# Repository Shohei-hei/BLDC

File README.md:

# BLDC
BLDC hardware and software

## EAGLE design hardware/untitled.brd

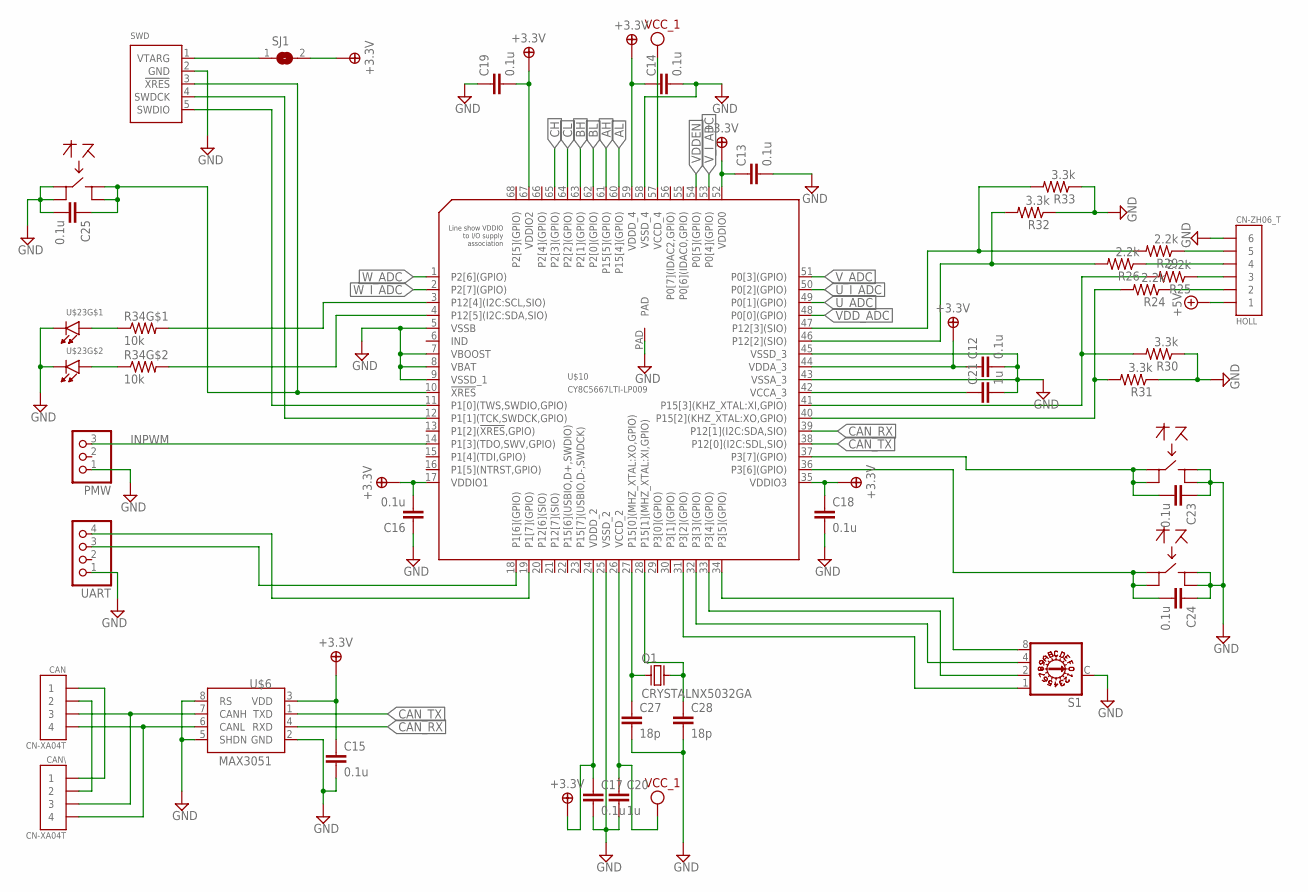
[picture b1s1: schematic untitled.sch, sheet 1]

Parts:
C12, C13, C14, C15, C16, C17, C18, C19, C23, C24, C25: 0.1u; C1005
C20, C21: 1u; C1608
C27, C28: 18p; C1608
CAN: CN-XA04T; XA04
CAN\: CN-XA04T; XA04
HOLL: CN-ZH06_T; ZH06
PMW: PINHD-1X03_2.54-S; 1X03-S
Q1: CRYSTALNX5032GA; NX5032GA
R24, R25, R26, R29: 2.2k; R1005
R30, R31, R32, R33: 3.3k; R1005
R34: 10k; R1005*2
RESET: SWITCH_4PALPS; SKRP
S1: P103_AKI; SW_ROT_5
SJ1: SJ
SWD: WRITE-FOR-PSOC3/4/5LP_ZH; ZH05
U$6: MAX3051; SOIC8
U$10: CY8C5667LTI-LP009; QFN68_8X8
U$23: LED2_SML522; LED1315
UART: PINHD-1X04_2.54-S; 1X04-S
USER1, USER2: SWITCH_4PALPS; SKRP

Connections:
3.3V: C12.1, C13.1, C14.1, C15.1, C16.2, C17.1, C18.1, C19.2, SJ1.2, U$6.3 (VDD), U$10.17 (VDDIO1), U$10.24 (VDDD_2), U$10.35 (VDDIO3), U$10.44 (VDDA_3), U$10.52 (VDDIO0), U$10.59 (VDDD_4), U$10.67 (VDDIO2); also elsewhere on the board
+5V: HOLL.1; also elsewhere on the board
AH: U$10.61 (P15[5](GPIO)); also elsewhere on the board
AL: U$10.60 (P15[4](GPIO)); also elsewhere on the board
BH: U$10.63 (P2[1](GPIO)); also elsewhere on the board
BL: U$10.62 (P2[0](GPIO)); also elsewhere on the board
CAN_RX: U$6.4 (RXD), U$10.39 (P12[1](I2C:SDA,SIO))
CAN_TX: U$6.1 (TXD), U$10.38 (P12[0](I2C:SDL,SIO))
CH: U$10.65 (P2[3](GPIO)); also elsewhere on the board
CL: U$10.64 (P2[2](GPIO)); also elsewhere on the board
GND: C12.2, C13.2, C14.2, C15.2, C16.1, C17.2, C18.2, C19.1, C20.2, C21.2, C23.1, C24.1, C25.2, C27.2, C28.2, HOLL.6, PMW.1, R30.1, R31.1, R32.1, R33.1, RESET.1, RESET.2, S1.C, SWD.2 (GND), U$6.2 (GND), U$6.5 (SHDN), U$6.8 (RS), U$10.5 (VSSB), U$10.7 (VBOOST), U$10.8 (VBAT), U$10.9 (VSSD_1), U$10.25 (VSSD_2), U$10.43 (VSSA_3), U$10.45 (VSSD_3), U$10.58 (VSSD_4), U$10.PAD, U$23.2 (C), U$23.4 (C), UART.1, USER1.3, USER1.4, USER2.3, USER2.4; also elsewhere on the board
INPWM: PMW.3, U$10.14 (P1[3](TDO,SWV,GPIO))
unnamed: U$10.18 (P1[6](GPIO)), UART.3
unnamed: S1.8, U$10.34 (P3[5](GPIO))
unnamed: R29.2, R33.2, U$10.47 (P12[3](SIO))
unnamed: C21.1, U$10.42 (VCCA_3)
unnamed: CAN.PIN1 (1), CAN\.PIN1 (1)
unnamed: CAN.PIN2 (2), CAN\.PIN2 (2)
unnamed: CAN.PIN3 (3), CAN\.PIN3 (3), U$6.7 (CANH)
unnamed: CAN.PIN4 (4), CAN\.PIN4 (4), U$6.6 (CANL)
unnamed: C23.2, U$10.37 (P3[7](GPIO)), USER1.1, USER1.2
unnamed: C24.2, U$10.36 (P3[6](GPIO)), USER2.1, USER2.2
unnamed: SWD.5 (SWDIO), U$10.11 (P1[0](TWS,SWDIO,GPIO))
unnamed: SWD.4 (SWDCK), U$10.12 (P1[1](TCK,SWDCK,GPIO))
unnamed: C27.1, Q1.1, U$10.27 (P15[0](MHZ_XTAL:XO,GPIO))
unnamed: C28.1, Q1.2, U$10.28 (P15[1](MHZ_XTAL:XI,GPIO))
unnamed: C25.1, RESET.3, RESET.4, SWD.3 (!XRES), U$10.10 (!XRES)
unnamed: U$10.19 (P1[7](GPIO)), UART.4
unnamed: S1.4, U$10.32 (P3[3](GPIO))
unnamed: S1.1, U$10.31 (P3[2](GPIO))
unnamed: R26.2, R32.2, U$10.46 (P12[2](SIO))
unnamed: S1.2, U$10.33 (P3[4](GPIO))
unnamed: R24.2, R31.2, U$10.40 (P15[2](KHZ_XTAL:XO,GPIO))
unnamed: R25.2, R30.2, U$10.41 (P15[3](KHZ_XTAL:XI,GPIO))
unnamed: HOLL.2, R24.1
unnamed: HOLL.3, R25.1
unnamed: HOLL.4, R26.1
unnamed: HOLL.5, R29.1
unnamed: SJ1.1, SWD.1 (VTARG)
unnamed: R34.A1 (1), U$23.1 (A)
unnamed: R34.B1 (1), U$23.3 (A)
unnamed: R34.B2 (2), U$10.4 (P12[5](I2C:SDA,SIO))
unnamed: R34.A2 (2), U$10.3 (P12[4](I2C:SCL,SIO))
U_ADC: U$10.49 (P0[1](GPIO)); also elsewhere on the board
U_I_ADC: U$10.50 (P0[2](GPIO)); also elsewhere on the board
VCC_1: C20.1, U$10.26 (VCCD_2), U$10.57 (VCCD_4)
VDDEN: U$10.54 (P0[5](GPIO)); also elsewhere on the board
VDD_ADC: U$10.48 (P0[0](GPIO)); also elsewhere on the board
V_ADC: U$10.51 (P0[3](GPIO)); also elsewhere on the board
V_I_ADC: U$10.53 (P0[4](GPIO)); also elsewhere on the board
W_ADC: U$10.1 (P2[6](GPIO)); also elsewhere on the board
W_I_ADC: U$10.2 (P2[7](GPIO)); also elsewhere on the board

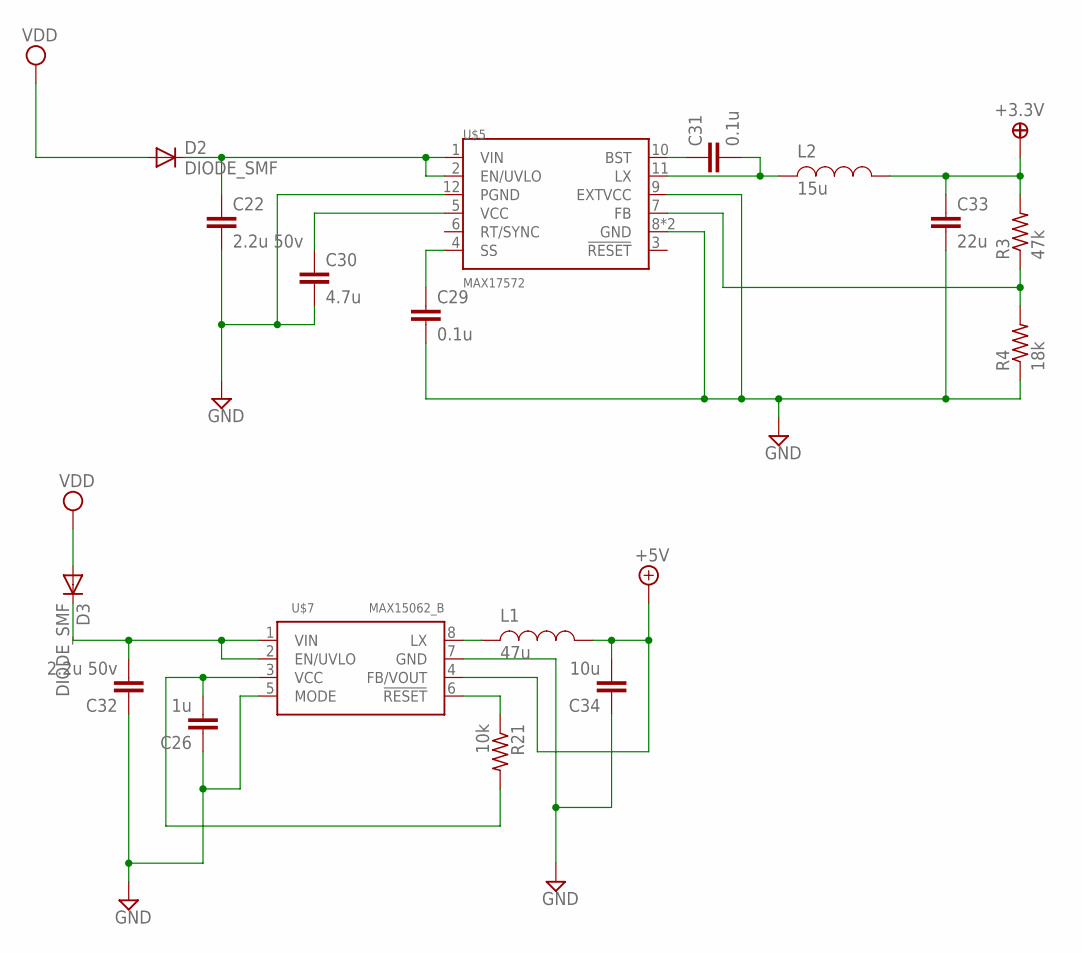
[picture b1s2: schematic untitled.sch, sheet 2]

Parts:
C22, C32: 2.2u 50v; C3216
C26: 1u; C1608
C29, C31: 0.1u; C1005
C30: 4.7u; C2012
C33: 22u; C3216
C34: 10u; C1608
D2, D3: DIODE_SMF; DO-219AB(SMF)
L1: 47u; L2518
L2: 15u; SRN4018
R3: 47k; R1005
R4: 18k; R1005
R21: 10k; R1005
U$5: MAX17572; TDFN12-3X3
U$7: MAX15062_B; TDFN08_2X2(NO_BOTTOM)

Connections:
3.3V: C33.1, L2.P$2, R3.2; also elsewhere on the board
+5V: C34.2, L1.P$2, U$7.4 (FB/VOUT); also elsewhere on the board
GND: C22.2, C26.1, C29.2, C30.2, C32.1, C33.2, C34.1, R4.1, U$5.8 (GND), U$5.9 (EXTVCC), U$5.12 (PGND), U$5.EPAD (GND), U$7.5 (MODE), U$7.7 (GND); also elsewhere on the board
unnamed: C32.2, D3.C, U$7.1 (VIN), U$7.2 (EN/UVLO)
unnamed: C22.1, D2.C, U$5.1 (VIN), U$5.2 (EN/UVLO)
unnamed: C29.1, U$5.4 (SS)
unnamed: C30.1, U$5.5 (VCC)
unnamed: R3.1, R4.2, U$5.7 (FB)
unnamed: C31.2, L2.P$1, U$5.11 (LX)
unnamed: C31.1, U$5.10 (BST)
unnamed: C26.2, R21.2, U$7.3 (VCC)
unnamed: R21.1, U$7.6 (!RESET)
unnamed: L1.P$1, U$7.8 (LX)
VDD: D2.A, D3.A; also elsewhere on the board

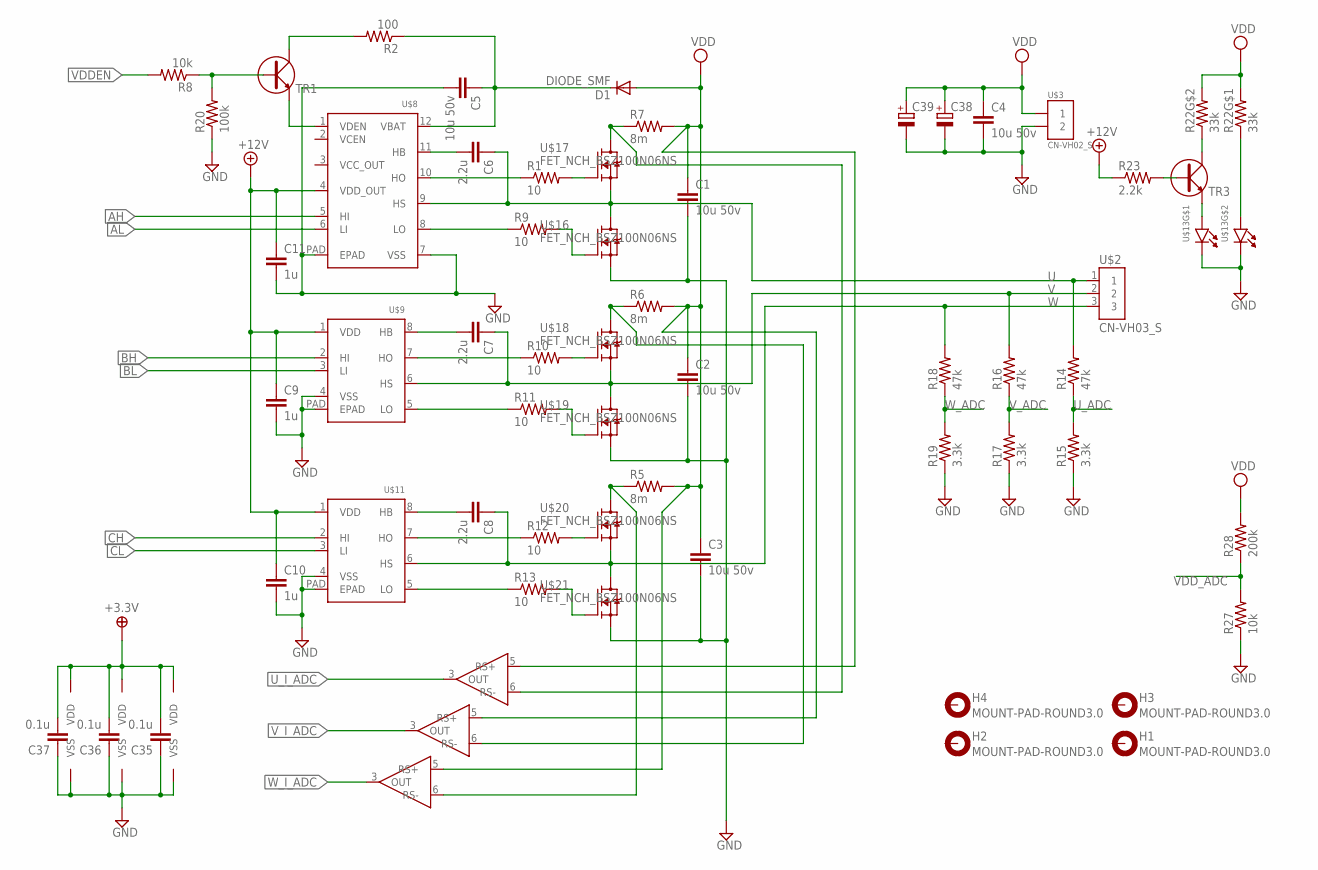
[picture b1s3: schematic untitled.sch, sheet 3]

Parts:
C1, C2, C3, C4, C5: 10u 50v; C3216
C6, C7, C8: 2.2u; C1005
C9, C10, C11: 1u; C1608
C35, C36, C37: 0.1u; C1005
C38: CPOL-EUG; PANASONIC_G
C39: CPOL-EUE5-13; E5-13
D1: DIODE_SMF; DO-219AB(SMF)
H1, H2, H3, H4: MOUNT-PAD-ROUND3.0; 3,0-PAD
R1, R9, R10, R11, R12, R13: 10; R1608
R2: 100; R1005
R5, R6, R7: 8m; R3216
R8, R27: 10k; R1005
R14, R16, R18: 47k; R1005
R15, R17, R19: 3.3k; R1005
R20: 100k; R1005
R22: 33k; R1005*2
R23: 2.2k; R1005
R28: 200k; R1005
TR1, TR3: TR_NTR; SOT-23-3
U$2: CN-VH03_S; VH03-S
U$3: CN-VH02_S; VH02-S
U$8: HIP2104; DFN_4X4_12LD
U$9, U$11: HIP2103; DFN_3X3_8L
U$13: LED2_SML522; LED1315
U$14, U$15, U$22: MAX40010; SOT-23-6
U$16, U$17, U$18, U$19, U$20, U$21: FET_NCH_BSZ100N06NS; TSDSON-8

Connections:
3.3V: C35.2, C36.2, C37.2, U$14.4 (VDD), U$15.4 (VDD), U$22.4 (VDD); also elsewhere on the board
+12V: C9.1, C10.1, C11.1, R23.1, U$8.4 (VDD_OUT), U$9.1 (VDD), U$11.1 (VDD)
AH: U$8.5 (HI); also elsewhere on the board
AL: U$8.6 (LI); also elsewhere on the board
BH: U$9.2 (HI); also elsewhere on the board
BL: U$9.3 (LI); also elsewhere on the board
CH: U$11.2 (HI); also elsewhere on the board
CL: U$11.3 (LI); also elsewhere on the board
GND: C1.2, C2.2, C3.2, C4.2, C5.2, C9.2, C10.2, C11.2, C35.1, C36.1, C37.1, C38.-, C39.-, R15.1, R17.1, R19.1, R20.1, R27.1, U$3.1 (2), U$8.7 (VSS), U$8.PAD (EPAD), U$9.4 (VSS), U$9.PAD (EPAD), U$11.4 (VSS), U$11.PAD (EPAD), U$13.2 (C), U$13.4 (C), U$14.2 (VSS), U$15.2 (VSS), U$16.1 (S), U$16.2 (S), U$16.3 (S), U$16.123 (S), U$19.1 (S), U$19.2 (S), U$19.3 (S), U$19.123 (S), U$21.1 (S), U$21.2 (S), U$21.3 (S), U$21.123 (S), U$22.2 (VSS); also elsewhere on the board
unnamed: R13.2, U$21.4 (G)
unnamed: R13.1, U$11.5 (LO)
unnamed: R11.2, U$19.4 (G)
unnamed: R12.1, U$11.7 (HO)
unnamed: R9.2, U$16.4 (G)
unnamed: R12.2, U$20.4 (G)
unnamed: R6.1, U$15.6 (RS-), U$18.5 (D), U$18.6 (D), U$18.7 (D), U$18.8 (D), U$18.5678 (D)
unnamed: C8.2, U$11.8 (HB)
unnamed: C7.2, U$9.8 (HB)
unnamed: C6.2, U$8.11 (HB)
unnamed: R5.1, U$20.5 (D), U$20.6 (D), U$20.7 (D), U$20.8 (D), U$20.5678 (D), U$22.6 (RS-)
unnamed: TR1.2 (E), U$8.1 (VDEN)
unnamed: R8.1, R20.2, TR1.1 (B)
unnamed: R11.1, U$9.5 (LO)
unnamed: R10.2, U$18.4 (G)
unnamed: R10.1, U$9.7 (HO)
unnamed: R9.1, U$8.8 (LO)
unnamed: R2.2, TR1.3 (C)
unnamed: R7.1, U$14.6 (RS-), U$17.5 (D), U$17.6 (D), U$17.7 (D), U$17.8 (D), U$17.5678 (D)
unnamed: C5.1, D1.C, R2.1, U$8.12 (VBAT)
unnamed: R23.2, TR3.1 (B)
unnamed: R1.2, U$17.4 (G)
unnamed: R1.1, U$8.10 (HO)
unnamed: R22.B1 (1), TR3.3 (C)
unnamed: TR3.2 (E), U$13.1 (A)
unnamed: R22.A1 (1), U$13.3 (A)
U: C6.1, R14.2, U$2.1, U$8.9 (HS), U$16.5 (D), U$16.6 (D), U$16.7 (D), U$16.8 (D), U$16.5678 (D), U$17.1 (S), U$17.2 (S), U$17.3 (S), U$17.123 (S)
U_ADC: R14.1, R15.2; also elsewhere on the board
U_I_ADC: U$14.3 (OUT); also elsewhere on the board
V: C7.1, R16.2, U$2.2, U$9.6 (HS), U$18.1 (S), U$18.2 (S), U$18.3 (S), U$18.123 (S), U$19.5 (D), U$19.6 (D), U$19.7 (D), U$19.8 (D), U$19.5678 (D)
VDD: C1.1, C2.1, C3.1, C4.1, C38.+, C39.+, D1.A, R5.2, R6.2, R7.2, R22.A2 (2), R22.B2 (2), R28.2, U$3.2 (1), U$14.5 (RS+), U$15.5 (RS+), U$22.5 (RS+); also elsewhere on the board
VDDEN: R8.2; also elsewhere on the board
VDD_ADC: R27.2, R28.1; also elsewhere on the board
V_ADC: R16.1, R17.2; also elsewhere on the board
V_I_ADC: U$15.3 (OUT); also elsewhere on the board
W: C8.1, R18.2, U$2.3, U$11.6 (HS), U$20.1 (S), U$20.2 (S), U$20.3 (S), U$20.123 (S), U$21.5 (D), U$21.6 (D), U$21.7 (D), U$21.8 (D), U$21.5678 (D)
W_ADC: R18.1, R19.2; also elsewhere on the board
W_I_ADC: U$22.3 (OUT); also elsewhere on the board

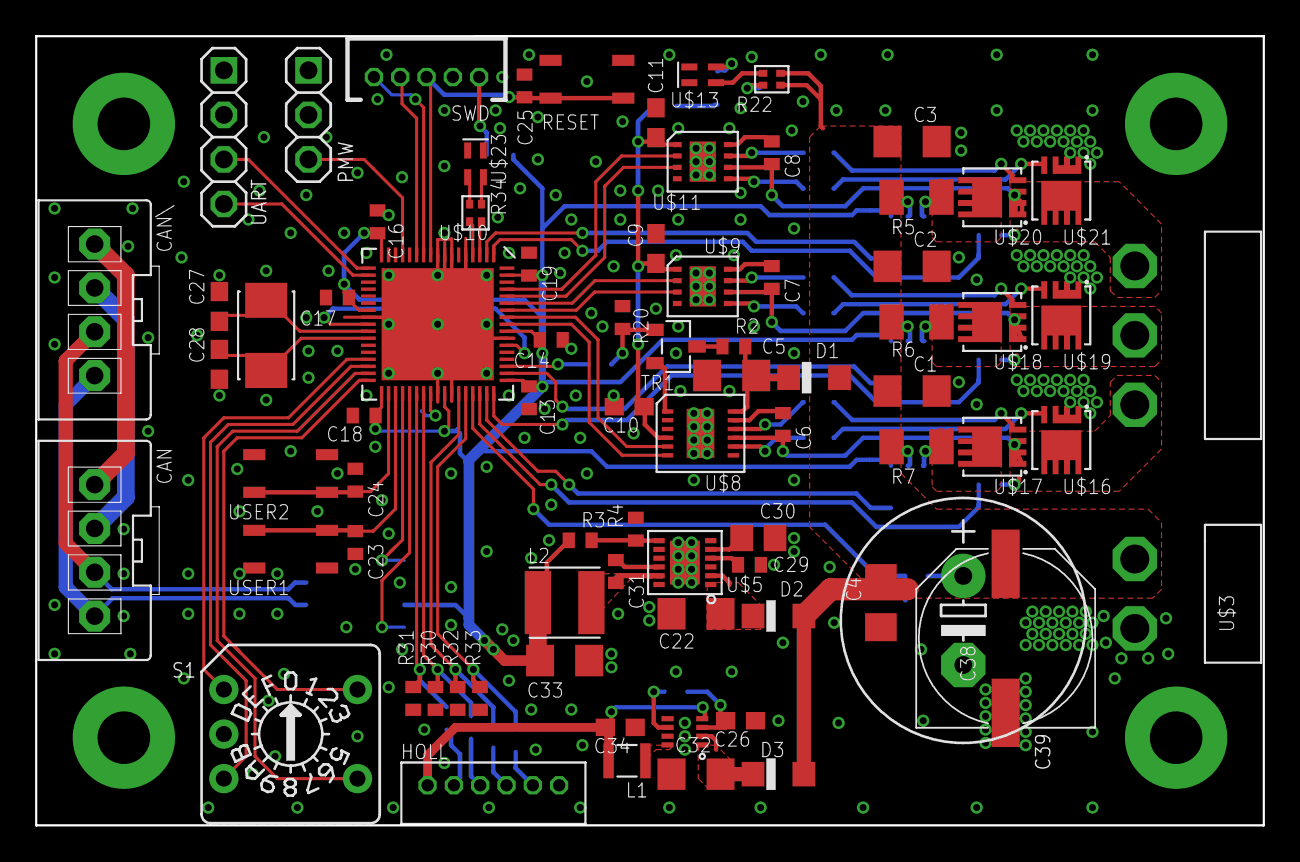
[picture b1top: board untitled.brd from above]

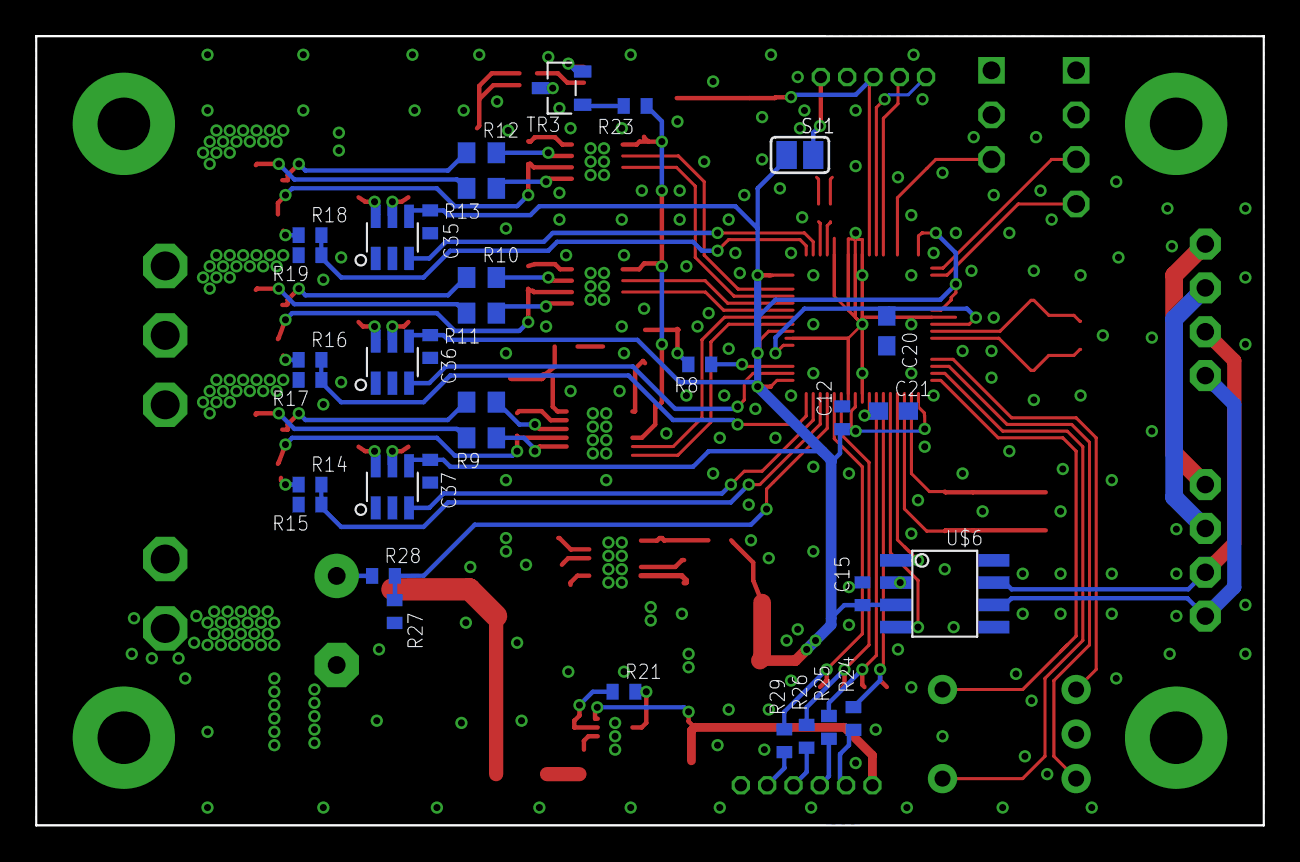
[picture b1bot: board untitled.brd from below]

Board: 2 copper layers, 70.0 x 45.0 mm, 116 parts (34 on the bottom side), 93 nets.

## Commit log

2018-02-09 add hardware file and software file
    Hardware is designed by EAGLE.
    Software is PSoC5LP
